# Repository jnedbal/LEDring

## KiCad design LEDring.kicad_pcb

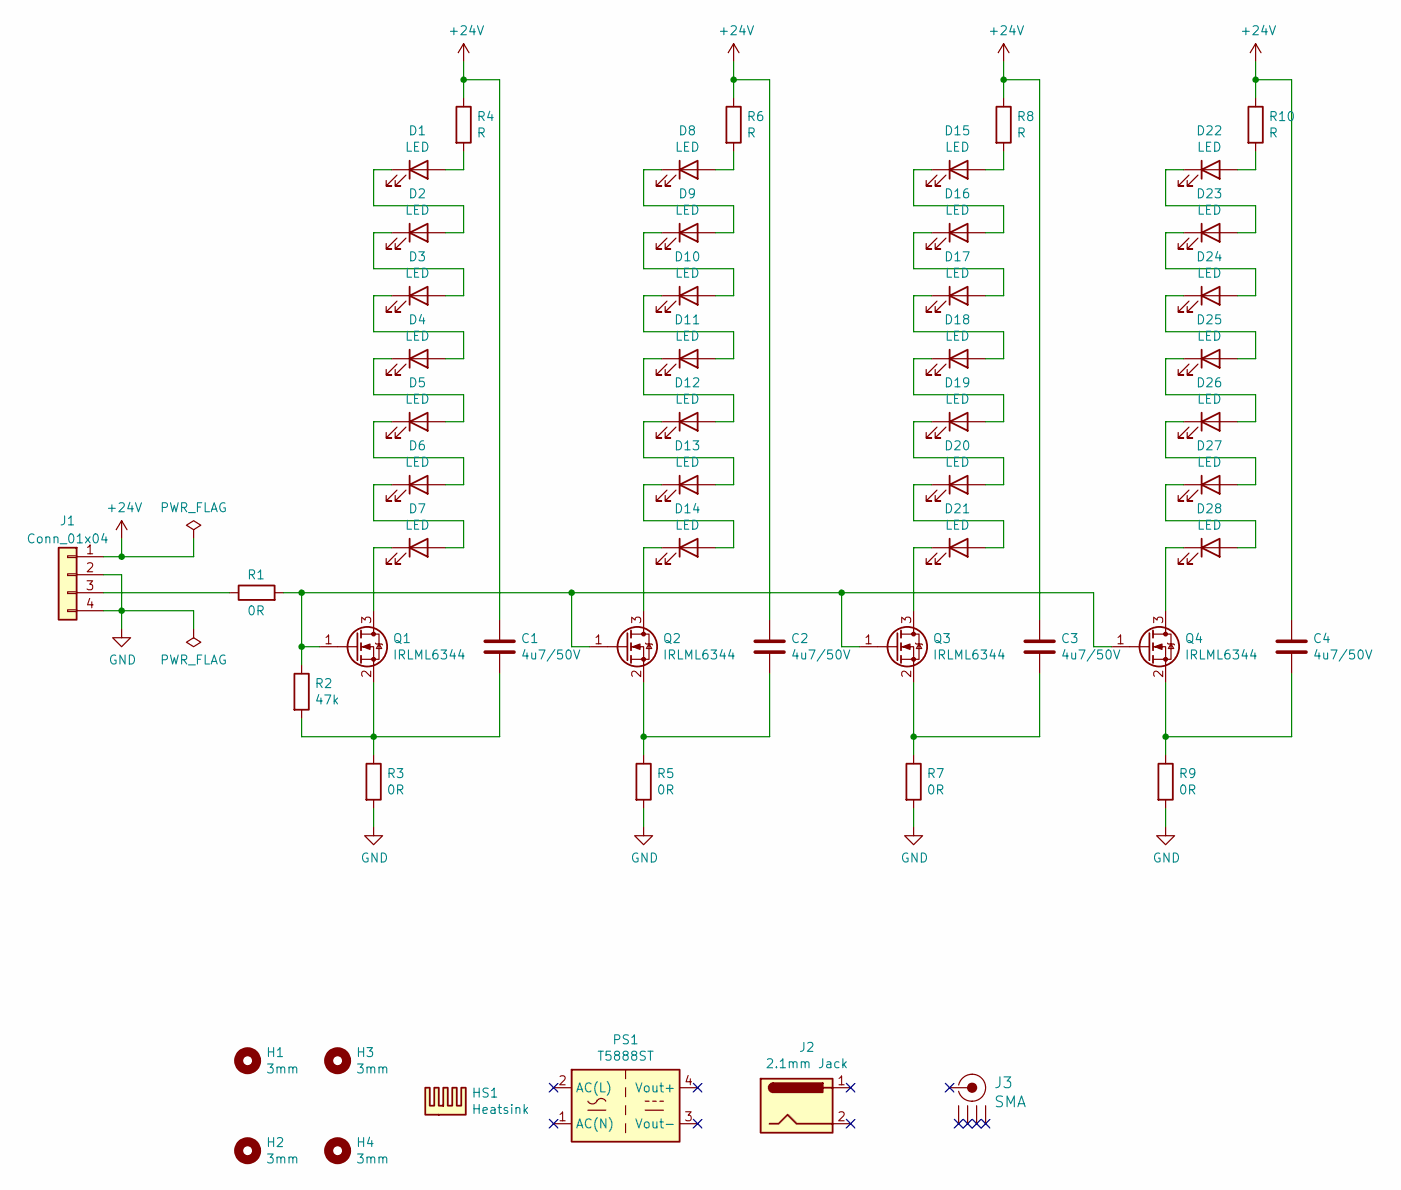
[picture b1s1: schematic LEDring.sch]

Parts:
C1, C2, C3, C4: 4u7/50V; C_1206_3216Metric; Part Number GRM31CR71H475KA12L
D1, D2, D3, D4, D5, D6, D7, D8, D9, D10, D11, D12, D13, D14, D15, D16, D17, D18, D19, D20, D21, D22, D23, D24, D25, D26, D27, D28: LED; LED_Cree_PLCC2; Part Number CLM3C-WKW-CWBYA453
H1, H2, H3, H4: 3mm; MountingHole_3.2mm_M3
HS1: Heatsink; Part Number ICK PGA 17 X17
J1: Conn_01x04; PinHeader_1x04_P2.54mm_Vertical_SMD_Pin1Left
J2: 2.1mm Jack; Part Number FC681473
J3: SMA; Part Number MC002126
PS1: T5888ST; Part Number T5888ST
Q1, Q2, Q3, Q4: IRLML6344; SOT-23; Part Number IRLML6344TRPBF
R1, R3, R5, R7, R9: 0R; R_1206_3216Metric; Part Number MCWR12X000 PTL
R2: 47k; R_0603_1608Metric
R4, R6, R8, R10: R; R_1206_3216Metric

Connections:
+24V: C1.1, C2.1, C3.1, C4.1, J1.1, R4.1, R6.1, R8.1, R10.1
GND: J1.2, J1.4, R3.2, R5.2, R7.2, R9.2
unnamed: C1.2, Q1.2 (S), R2.2, R3.1
unnamed: C2.2, Q2.2 (S), R5.1
unnamed: C3.2, Q3.2 (S), R7.1
unnamed: C4.2, Q4.2 (S), R9.1
unnamed: D1.1 (K), D2.2 (A)
unnamed: D1.2 (A), R4.2
unnamed: D2.1 (K), D3.2 (A)
unnamed: D3.1 (K), D4.2 (A)
unnamed: D4.1 (K), D5.2 (A)
unnamed: D5.1 (K), D6.2 (A)
unnamed: D6.1 (K), D7.2 (A)
unnamed: D7.1 (K), Q1.3 (D)
unnamed: D8.1 (K), D9.2 (A)
unnamed: D8.2 (A), R6.2
unnamed: D10.1 (K), D11.2 (A)
unnamed: D9.1 (K), D10.2 (A)
unnamed: D11.1 (K), D12.2 (A)
unnamed: D12.1 (K), D13.2 (A)
unnamed: D13.1 (K), D14.2 (A)
unnamed: D14.1 (K), Q2.3 (D)
unnamed: D15.1 (K), D16.2 (A)
unnamed: D15.2 (A), R8.2
unnamed: D16.1 (K), D17.2 (A)
unnamed: D17.1 (K), D18.2 (A)
unnamed: D18.1 (K), D19.2 (A)
unnamed: D19.1 (K), D20.2 (A)
unnamed: D20.1 (K), D21.2 (A)
unnamed: D21.1 (K), Q3.3 (D)
unnamed: D22.1 (K), D23.2 (A)
unnamed: D22.2 (A), R10.2
unnamed: D23.1 (K), D24.2 (A)
unnamed: D24.1 (K), D25.2 (A)
unnamed: D25.1 (K), D26.2 (A)
unnamed: D26.1 (K), D27.2 (A)
unnamed: D27.1 (K), D28.2 (A)
unnamed: D28.1 (K), Q4.3 (D)
unnamed: J1.3, R1.1
unnamed: Q1.1 (G), Q2.1 (G), Q3.1 (G), Q4.1 (G), R1.2, R2.1

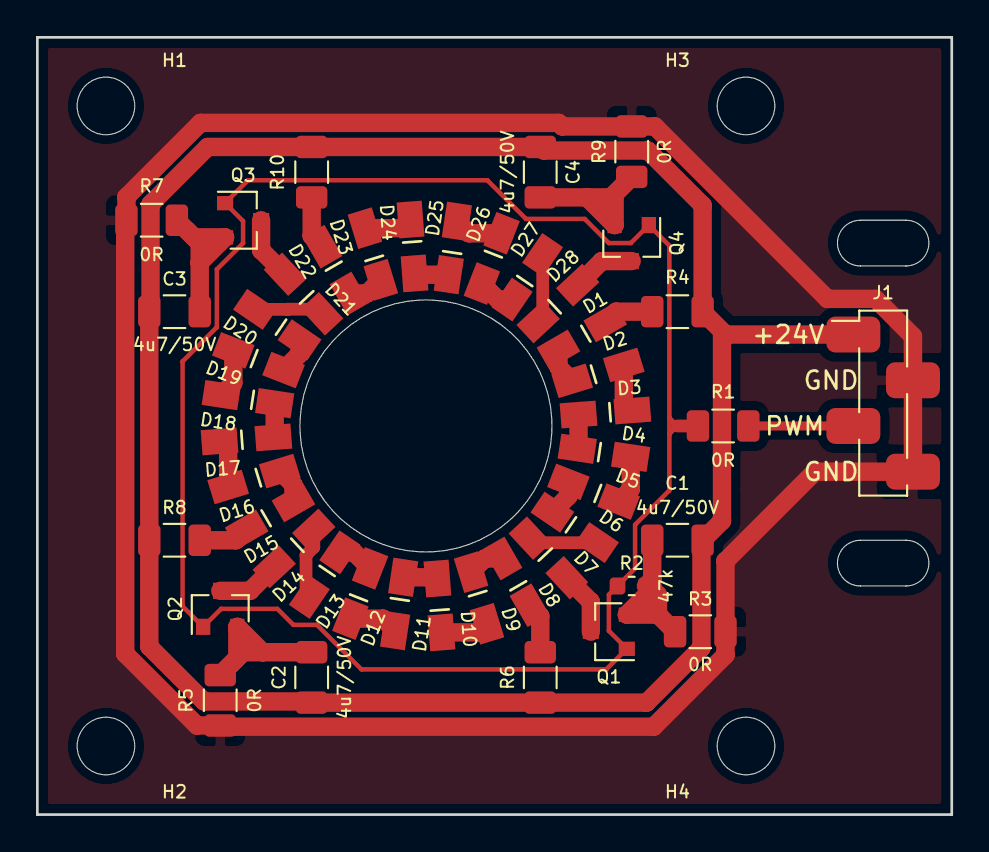
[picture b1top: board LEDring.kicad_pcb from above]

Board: 2 copper layers, 50.8 x 43.2 mm, 51 parts (0 on the bottom side), 40 nets.

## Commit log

2020-11-24 Initial commit with 28 LEDs.
